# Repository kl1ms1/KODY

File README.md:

# KODY

Карманный мультитул-девайс: **плата расширения для Raspberry Pi Zero** с цветным
тачскрином, крутилкой, кнопками, антеннами (Sub-GHz, LoRa, 2.4 ГГц, SDR),
NFC/RFID, ИК, USB-C зарядкой, USB-A портами и выведенной наверх гребёнкой
на 40 GPIO для своих проектов.

> **Актуальная версия — v9:** [`docs/kody-v9.md`](docs/kody-v9.md) — экран 3.5″ 60 Гц, ≈3 часа, крутилка без упора, переключатель питания, мощный ИК-порт, один USB-C, хакерский принт; что купить — [`docs/shopping-list.md`](docs/shopping-list.md);
> отпечаток почти как у самой Pi. Смотри [`docs/concept.md`](docs/concept.md) и
> **3D-модель с телефона:** https://claude.ai/artifact/SPZszNhs2kebLbU7mErjtX
>
> Ниже — первый разбор идеи (v1, одна большая плата). Механика оттуда устарела,
> но разбор радио/NFC/питания по-прежнему актуален.

## Это реализуемо?

**Да.** Почти всё из идеи делается на готовых и доступных компонентах.
Несколько вещей нужно сделать чуть иначе, чем задумано — коротко:

| Хотелка | Вердикт | Как именно |
|---|---|---|
| Плата, которая вставляется в Pi Zero | ✅ | Основная плата с гнездом 2×20, Pi Zero сидит на ней «бутербродом» |
| Очень хороший экран, много герц, тачскрин | ✅ с оговоркой | У Pi Zero нет DSI-разъёма. Лучший вариант: 2.8" IPS 320×240 по SPI (ST7789) + ёмкостный тач (FT6336) — **40–50 FPS**, плавно и ярко. Большой 4–5" экран возможен только по HDMI (дороже, толще, жрёт батарею) |
| Крутилка «как громкость в машине», очень плавная | ✅ | Магнитный энкодер **AS5600** + металлическая ручка на подшипнике с демпферной смазкой: без щелчков, бесконечное вращение, 4096 положений на оборот |
| 2–3 кнопки | ✅ | |
| Антенны SDR / LoRa / Sub-GHz / NRF24 | ✅ | RTL-SDR (USB), SX1262 (LoRa), CC1101 (Sub-GHz как у флиппера), NRF24L01+PA/LNA. Сзади 4 разъёма SMA |
| ИК | ✅ | ИК-приёмник + мощные ИК-диоды |
| NFC/RFID «своя плата, не PN532» | ✅ | **ST25R3916** (13.56 МГц: чтение **и эмуляция** — тот же чип, что во Flipper Zero) + схема 125 кГц на микроконтроллере |
| Слот для «сим-карты» под локальные файлы | ✅ но это **microSD** | В SIM-карту файлы записать нельзя. Делаем второй слот microSD — он отдельный от системной карты Pi |
| Зарядка по USB-C | ✅ | Контроллер BQ25895 (заряд + питание + повышение до 5 В) и Li-Po аккумулятор |
| 2–3 USB-A («квадратный, который всегда не той стороной») | ✅ | USB-хаб на плате (FE1.1s). У Pi Zero один USB, хаб размножает его |
| Все 40 GPIO наверх «мамой» | ✅ | Все 40 линий проходят насквозь на гнездо 2×20 сверху. Занятые девайсом пины подписаны на шелкографии, а программа не даст их случайно занять |
| Меню «Проекты → Лампочка → пресеты → мигание/плавно» | ✅ | Прототип уже здесь: [`software/`](software/) |

### Две важные рекомендации

1. **Возьми Raspberry Pi Zero 2 W (или Zero 2 WH)** вместо Zero WH.
   Размер и разъём те же — плата подойдёт к обоим. Но у Zero WH одно слабое
   ядро ARMv6: плавный интерфейс + SDR на нём будут тормозить. Zero 2 W в 4–5
   раз быстрее и стоит ~$15. Для первого прототипа Zero WH сгодится.
2. **Всё, что требует точного тайминга (Sub-GHz запись/повтор, NFC-эмуляция,
   125 кГц, ИК, кнопки, крутилка), повесить на сопроцессор RP2040**.
   Linux не умеет в микросекундную точность, а микроконтроллер — умеет. Так
   же сделано во Flipper Zero. Заодно это освобождает пины Pi для твоих проектов.

## Документы

- [`docs/concept.md`](docs/concept.md) — **v5 вертикальный** (варианты А/Б) и v4: платы, что можно/нельзя, распиновка.
- [`docs/shopping-list.md`](docs/shopping-list.md) и страница https://claude.ai/artifact/PkMxhhZDHSbbQT44wBgvSS — что купить, со ссылками на поиск
  по Ozon, Wildberries, Я.Маркету, AliExpress и ЧипДипу.
- [`docs/hardware.md`](docs/hardware.md) — (v1) архитектура, распиновка всех 40 GPIO,
  питание, список компонентов (BOM) и цены, пошаговый план в EasyEDA.
- [`docs/roadmap.md`](docs/roadmap.md) — этапы от макетки до продаваемого
  устройства, и что нужно для продажи (сертификация, законность).
- [`software/`](software/) — прототип ПО: раздел «Проекты», проект «Лампочка».

## Быстрый старт программы

```bash
cd software
python3 -m kody            # на ПК работает в режиме симуляции
sudo apt install python3-gpiozero && python3 -m kody   # на Raspberry Pi — реальные пины
python3 -m unittest -v     # тесты
```

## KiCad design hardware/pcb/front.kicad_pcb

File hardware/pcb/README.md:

# Платы KODY v9 — этап 1 (механика и разъёмы)

**Наглядно, что где и зачем:** https://claude.ai/artifact/89wcDY2xsGRGSkXmGNxgyf — страница `docs/pcb/kody-pcb-guide.html` (генерируется `tools/gen_pcb_guide.py`).

Изменения: радиомодули стоят у своих антенн (NRF24, GPS, LoRa — наверху); рация SA818 и CC1101 — внизу, к антенне «Рация 433» короткий кабель с защёлками; ESP32-C5 убран (Wi-Fi/Bluetooth у Pi свои); контуры и подписи всех модулей нарисованы шелкографией на самой плате.

| Передняя | Задняя (вид снаружи) |
|---|---|
|  |  |

Файлы KiCad 7: `front.kicad_pcb`, `back.kicad_pcb` (генерируются `generate_boards.py`).

## Что уже сделано

**Обе платы:** контур 51.6 × 99.6 мм, отверстия под Pi Zero (M2.5) и под корпус
(M2), разъём плата-плата 2×12 1.27 мм (SMD) внизу слева — контакт 1 на обеих
платах в одной точке, цепи подписаны.

**Передняя:**
- J1 — гнездо, сквозь которое проходит гребёнка Pi (раскладка как у Pi, вид сверху);
- J2 — угловое гнездо GPIO на левом краю, **все 40 линий разведены пин в пин**;
- правый край сверху вниз: крутилка EC11/PEC12R (угловая, с кнопкой), 3 кнопки 6×6 угловые, ползунок питания SS12D07/OS102011;
- верхний край: 4 гнезда SMA (LoRa, рация, 2.4 ГГц, GPS);
- нижний край: один USB-C (данные + PD), 4 светодиода индикатора заряда;
- левый край под GPIO: ИК-порт (2× VSLY5940 + 2× TSAL6400), над GPIO — 2 ИК-приёмника;
- разъёмы FPC экрана и HDMI-шлейфа (модель разъёма уточним под купленный экран);
- 3 площадки под лепестки аккумулятора;
- разметкой: места модулей (рация SA818, LoRa, CC1101, NRF24, ESP32-C5, GPS), аккумулятор, динамик, контур Pi.

**Задняя:**
- катушка NFC 13.56 МГц дорожками (4 витка) + площадки к согласованию;
- место и площадки большой намотанной катушки 125 кГц по периметру всей спины;
- pogo-площадки к низу Pi (USB + питание) — **точные места снимем с Pi штангенциркулем**;
- **чёрный череп + KODY** на шелкографии.

DRC KiCad: 0 ошибок меди между цепями. Оставшиеся замечания — края у
разъёмов, которые и должны выходить за край (SMA, USB-C, светодиоды ИК),
и пересечения «рамок» соседних светодиодов (сами корпуса не пересекаются);
несколько контактов разъёма плата-плата ещё не соединены — это сделает схема.

## Как открыть в EasyEDA Pro

1. EasyEDA Pro → **Файл → Импорт → KiCad**.
2. Выбрать `front.kicad_pcb` (потом так же `back.kicad_pcb`).
3. Если попросит проект целиком — запаковать папку `hardware/pcb` в zip.

## Что дальше (этап 2 — схема)

По блокам, каждый проверяется отдельно:
1. Питание: USB-C + CH224K + BQ25895 + DW01A/FS8205A + MAX17048 + TPS61088 + индикатор заряда.
2. Управление: STM32G031 + крутилка + кнопки + ползунок + DRV2605L.
3. Экран: LT6911C + разъём экрана (после проверки экрана на макетке).
4. Радио: RP2350 + SA818 + CC1101 + E22 + NRF24 + ESP32-C5 + GPS + ИК.
5. Задняя: USB2514B + TS3USB221 + TUSB320 + ST25R3916 + 125 кГц.

Перегенерировать: `/usr/bin/python3 hardware/pcb/generate_boards.py --drc`.

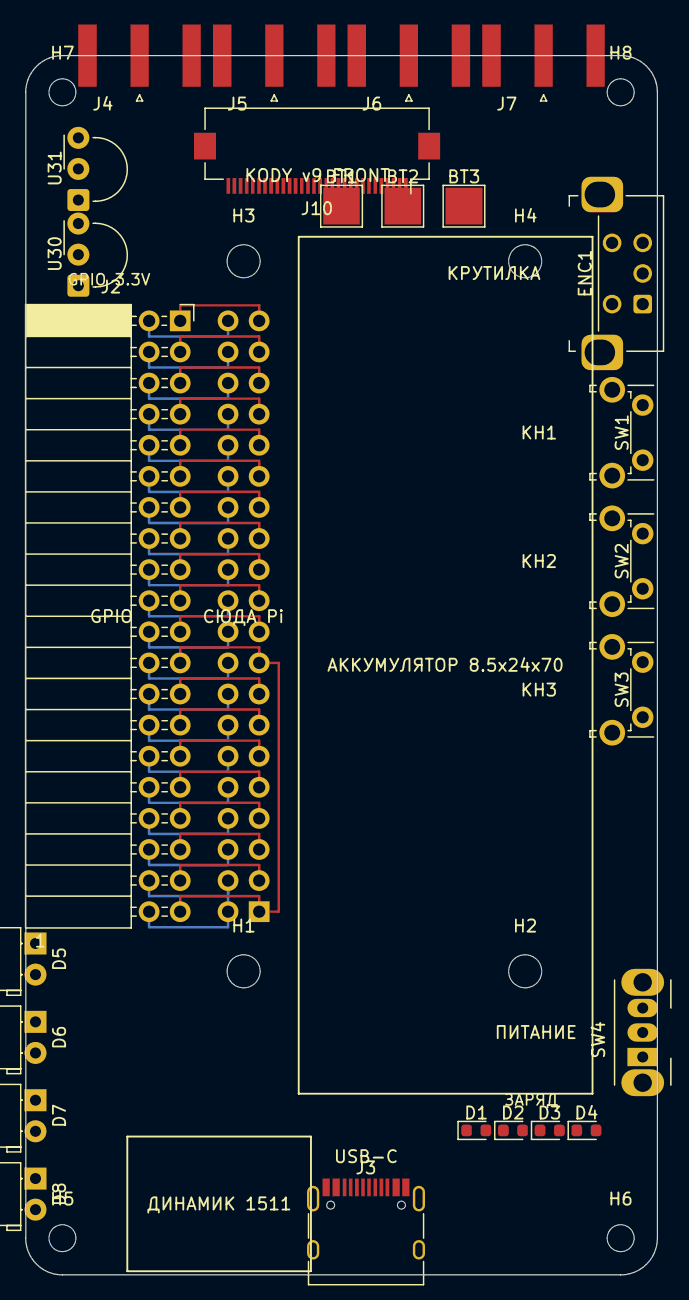
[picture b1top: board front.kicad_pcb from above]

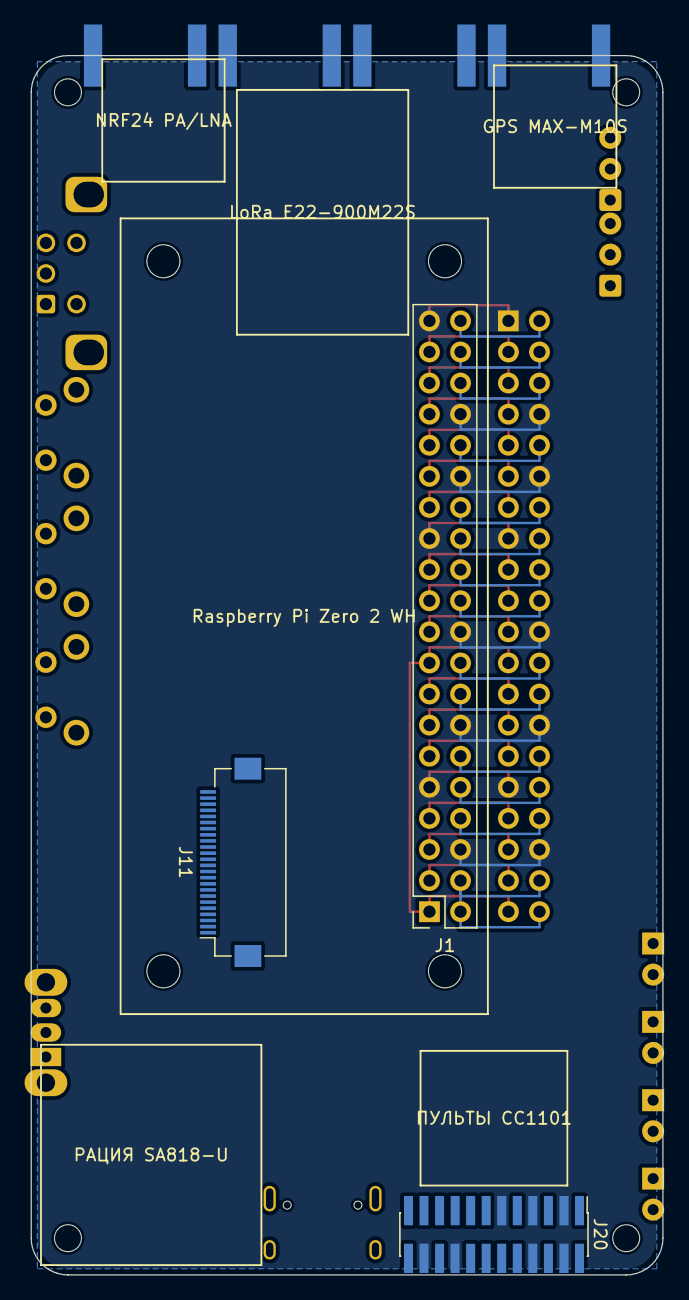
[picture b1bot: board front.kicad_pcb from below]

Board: 2 copper layers, 51.6 x 99.6 mm, 36 parts (3 on the bottom side), 31 nets.

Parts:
BT1: BAT+; TestPoint_Pad_3.0x3.0mm
BT2: BAT-; TestPoint_Pad_3.0x3.0mm
BT3: NTC; TestPoint_Pad_3.0x3.0mm
D1: Заряд 25%; LED_0603_1608Metric
D2: Заряд 50%; LED_0603_1608Metric
D3: Заряд 75%; LED_0603_1608Metric
D4: Заряд 100%; LED_0603_1608Metric
D5, D8: VSLY5940; LED_D5.0mm_Horizontal_O1.27mm_Z3.0mm
D6, D7: TSAL6400; LED_D5.0mm_Horizontal_O1.27mm_Z3.0mm
ENC1: EC11/PEC12R horizontal + push; RotaryEncoder_Bourns_Horizontal_PEC12R-2x17F-Sxxxx
H1, H2, H3, H4: Pi M2.5; MountingHole_2.7mm_M2.5
H5, H6, H7, H8: корпус M2; MountingHole_2.2mm_M2
J1: Pi socket 2x20 bottom-entry; PinSocket_2x20_P2.54mm_Vertical
J2: GPIO 2x20 out (left edge); PinSocket_2x20_P2.54mm_Horizontal
J3: USB-C (данные + PD); USB_C_Receptacle_HRO_TYPE-C-31-M-12
J4: SMA GPS; SMA_Amphenol_132289_EdgeMount
J5: SMA LoRa; SMA_Amphenol_132289_EdgeMount
J6: SMA Рация 433; SMA_Amphenol_132289_EdgeMount
J7: SMA 2.4 ГГц; SMA_Amphenol_132289_EdgeMount
J10: Экран (FPC, уточнить); Hirose_FH12-30S-0.5SH_1x30-1MP_P0.50mm_Horizontal
J11: HDMI-шлейф от Pi (FPC); Hirose_FH12-24S-0.5SH_1x24-1MP_P0.50mm_Horizontal
J20: B2B 2x12 1.27 SMD (к другой плате); PinHeader_2x12_P1.27mm_Vertical_SMD
SW1, SW2, SW3: Кнопка 6x6 угловая; SW_Tactile_SPST_Angled_PTS645Vx31-2LFS
SW4: Питание: ползунок SS12D07; SW_Slide_SPDT_Angled_CK_OS102011MA1Q
U30: TSOP38238; Vishay_MINIMOLD-3Pin
U31: TSMP58000; Vishay_MINIMOLD-3Pin

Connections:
+3V3: J1.1, J1.17, J2.23, J2.39, J20.12
+5V: J1.2, J1.4, J2.38, J2.40, J20.1, J20.2
GND: J1.6, J1.9, J1.14, J1.20, J1.25, J1.30, J1.34, J1.39, J2.1, J2.8, J2.12, J2.15, J2.22, J2.28, J2.31, J2.36, J20.3, J20.4, J20.7, J20.8, J20.11, J20.18, J20.22
GPIO2_SDA1: J1.3, J2.37
GPIO3_SCL1: J1.5, J2.35
GPIO4: J1.7, J2.33
GPIO5: J1.29, J2.11
GPIO6: J1.31, J2.9
GPIO7_CE1: J1.26, J2.16
GPIO8_CE0: J1.24, J2.18
GPIO9_MISO: J1.21, J2.19
GPIO10_MOSI: J1.19, J2.21
GPIO11_SCLK: J1.23, J2.17
GPIO12: J1.32, J2.10
GPIO13: J1.33, J2.7
GPIO14_TXD: J1.8, J2.34
GPIO15_RXD: J1.10, J2.32
GPIO16: J1.36, J2.6
GPIO17: J1.11, J2.29
GPIO18: J1.12, J2.30
GPIO19: J1.35, J2.5
GPIO20: J1.38, J2.4
GPIO21: J1.40, J2.2
GPIO22: J1.15, J2.25
GPIO23: J1.16, J2.26
GPIO24: J1.18, J2.24
GPIO25: J1.22, J2.20
GPIO26: J1.37, J2.3
GPIO27: J1.13, J2.27
ID_SC: J1.28, J2.14
ID_SD: J1.27, J2.13

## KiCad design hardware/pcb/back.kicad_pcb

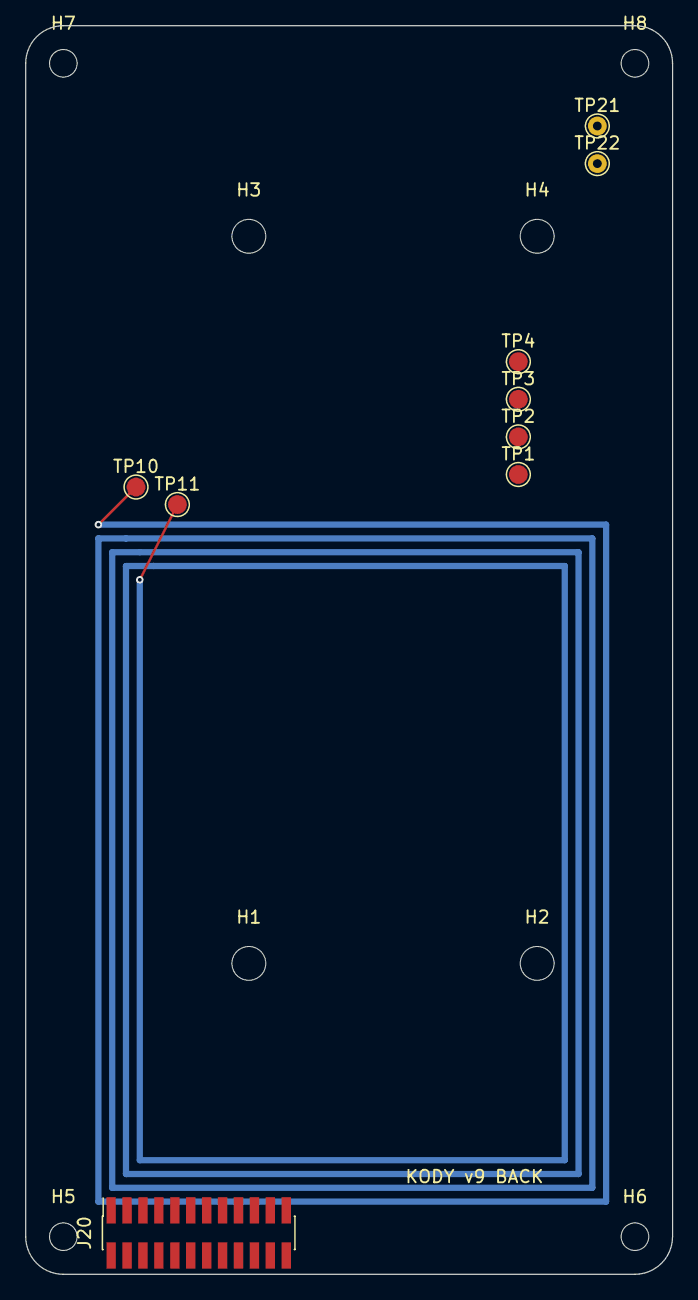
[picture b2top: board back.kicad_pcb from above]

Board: 2 copper layers, 51.6 x 99.6 mm, 17 parts (0 on the bottom side), 3 nets.

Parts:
H1, H2, H3, H4: Pi M2.5; MountingHole_2.7mm_M2.5
H5, H6, H7, H8: корпус M2; MountingHole_2.2mm_M2
J20: B2B 2x12 1.27 SMD (к другой плате); PinSocket_2x12_P1.27mm_Vertical_SMD
TP1: PI_5V; TestPoint_Pad_D1.5mm
TP2: GND; TestPoint_Pad_D1.5mm
TP3: PI_USB_DP; TestPoint_Pad_D1.5mm
TP4: PI_USB_DN; TestPoint_Pad_D1.5mm
TP10: NFC ANT1; TestPoint_Pad_D1.5mm
TP11: NFC ANT2; TestPoint_Pad_D1.5mm
TP21: COIL125_A; TestPoint_THTPad_D1.5mm_Drill0.7mm
TP22: COIL125_B; TestPoint_THTPad_D1.5mm_Drill0.7mm

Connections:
+5V: J20.1, J20.2
GND: J20.3, J20.4, J20.7, J20.8, J20.11, J20.18, J20.22, TP2.1
NFC_ANT1: TP10.1, TP11.1

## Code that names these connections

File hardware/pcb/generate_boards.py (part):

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TRACK = 0.2

PIN_NETS = {
    1: "+3V3", 2: "+5V", 3: "GPIO2_SDA1", 4: "+5V", 5: "GPIO3_SCL1", 6: "GND", 7: "GPIO4", 8: "GPIO14_TXD",
    9: "GND", 10: "GPIO15_RXD", 11: "GPIO17", 12: "GPIO18", 13: "GPIO27", 14: "GND", 15: "GPIO22", 16: "GPIO23",
    17: "+3V3", 18: "GPIO24", 19: "GPIO10_MOSI", 20: "GND", 21: "GPIO9_MISO", 22: "GPIO25", 23: "GPIO11_SCLK",
    24: "GPIO8_CE0", 25: "GND", 26: "GPIO7_CE1", 27: "ID_SD", 28: "ID_SC", 29: "GPIO5", 30: "GND", 31: "GPIO6",
    32: "GPIO12", 33: "GPIO13", 34: "GND", 35: "GPIO19", 36: "GPIO16", 37: "GPIO26", 38: "GPIO20", 39: "GND",
    40: "GPIO21",
}
B2B_NETS = ["+5V", "+5V", "GND", "GND", "USB1_DP", "USB1_DN", "GND", "GND", "USB2_DP", "USB2_DN", "GND", "+3V3",
            "NFC_SCK", "NFC_MOSI", "NFC_MISO", "NFC_CS", "NFC_IRQ", "GND", "RF125_TX", "RF125_RX", "RF125_MOD", "GND",
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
